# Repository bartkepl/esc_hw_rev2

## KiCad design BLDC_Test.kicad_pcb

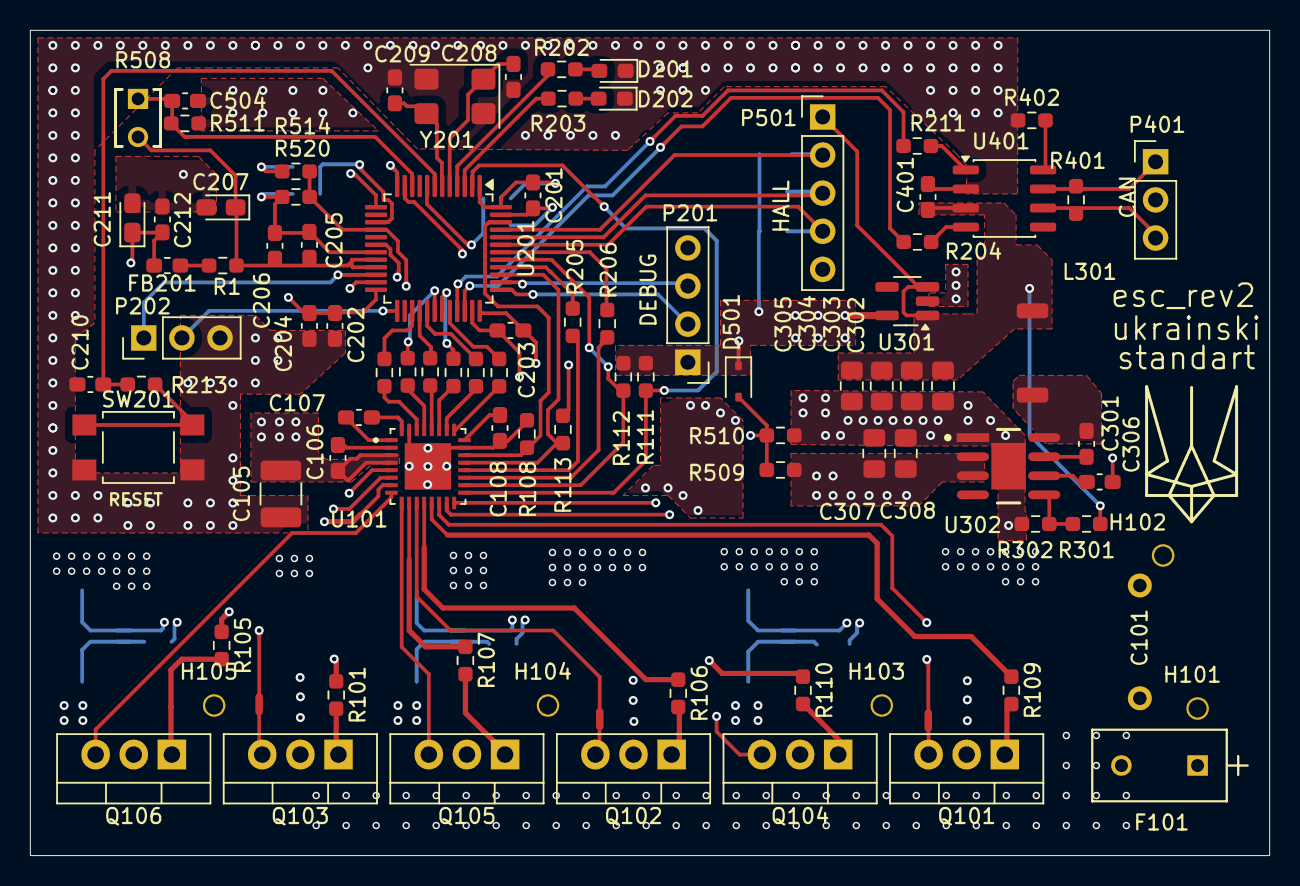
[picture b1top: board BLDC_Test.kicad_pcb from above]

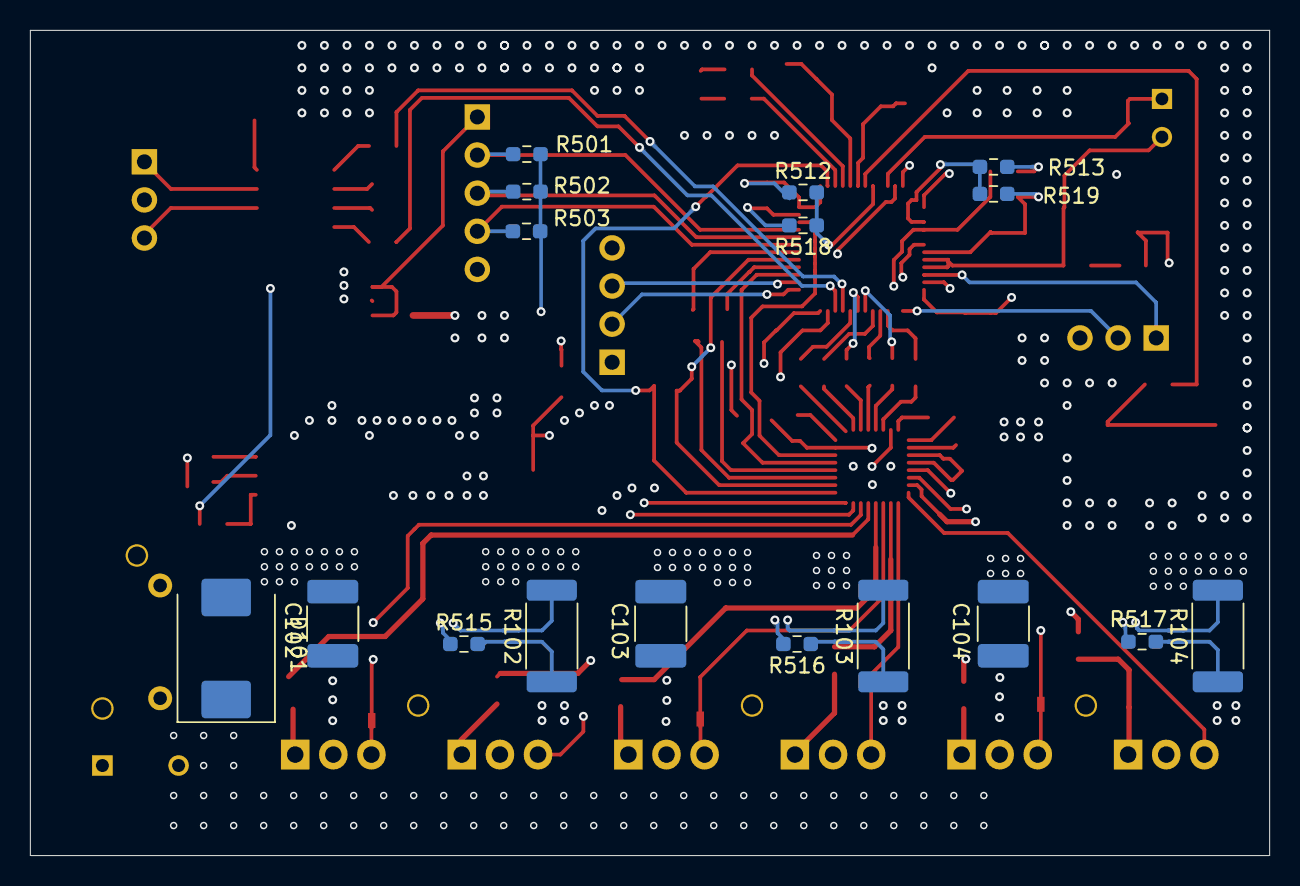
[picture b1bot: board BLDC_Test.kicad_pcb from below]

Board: 6 copper layers, 82.6 x 55.0 mm, 115 parts (23 on the bottom side), 89 nets.

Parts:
C101: 1000uF; PCAP_7_5mm
C102, C103, C104: 1812B105K101CT; C_1812_4532Metric_Pad1.57x3.40mm_HandSolder
C105: 0.1u; C_1210_3225Metric_Pad1.33x2.70mm_HandSolder
C106, C108, C306: 1u; C_0603_1608Metric_Pad1.08x0.95mm_HandSolder
C107: 47n; C_0603_1608Metric_Pad1.08x0.95mm_HandSolder
C201: 4.7uF; C_0603_1608Metric_Pad1.08x0.95mm_HandSolder
C202, C203, C204, C205, C206, C212: 100nF; C_0603_1608Metric_Pad1.08x0.95mm_HandSolder
C207, C211: 10uF; CP_EIA-2012-15_AVX-P_HandSolder
C208, C209: 33pF; C_0603_1608Metric_Pad1.08x0.95mm_HandSolder
C210, C301, C401: 100n; C_0603_1608Metric_Pad1.08x0.95mm_HandSolder
C302, C303, C304, C305: 22uF; C_0805_2012Metric_Pad1.18x1.45mm_HandSolder
C307: C3216X7R1H106K160AC; C_0805_2012Metric_Pad1.18x1.45mm_HandSolder
C308: KAF31BR71H224KT; C_0805_2012Metric_Pad1.18x1.45mm_HandSolder
C504: ?; C_0603_1608Metric_Pad1.08x0.95mm_HandSolder
D101: SMCJ36CA; D_SMC
D201, D202: Common diode; LED_0603_1608Metric_Pad1.05x0.95mm_HandSolder
D501: SS25FA; D_SOD-323
F101: SS-5F-10A-AP; FUSE_SS-5F_COB
FB201: BLM15BD601SZ1D; L_0603_1608Metric_Pad1.05x0.95mm_HandSolder
H101, H102, H103, H104, H105: phase connector; phase_cable_soldering_hole
L301: CDRH5D28RNP-8R0NC
NT101, NT102, NT103: net_tie; NetTie-2_SMD_Pad0.5mm
NT104, NT105, NT106, NT107, NT108, NT109: net_tie; NetTie-2_SMD_Pad0.3mm
P201: Header 4; PinHeader_1x04_P2.54mm_Vertical
P202, P401: Header 3; PinHeader_1x03_P2.54mm_Vertical
P501: Header 5; PinHeader_1x05_P2.54mm_Vertical
Q101, Q102, Q103, Q104, Q105, Q106: TK35A08N1; TO-220-3_Vertical
R1: 1; R_0603_1608Metric_Pad0.98x0.95mm_HandSolder
R101, R105, R106, R107, R109, R110: 10; R_0603_1608Metric_Pad0.98x0.95mm_HandSolder
R102, R103, R104: 20m; R_2512_6332Metric_Pad1.40x3.35mm_HandSolder
R108, R111, R113: 10k; R_0603_1608Metric_Pad0.98x0.95mm_HandSolder
R112: 1.8k; R_0603_1608Metric_Pad0.98x0.95mm_HandSolder
R201, R207, R208, R209, R210, R212, R213: 100; R_0603_1608Metric_Pad0.98x0.95mm_HandSolder
R202, R203: 220; R_0603_1608Metric_Pad0.98x0.95mm_HandSolder
R204, R205, R206, R211: 1k; R_0603_1608Metric_Pad0.98x0.95mm_HandSolder
R301: 100k; R_0603_1608Metric_Pad0.98x0.95mm_HandSolder
R302: 24.9k; R_0603_1608Metric_Pad0.98x0.95mm_HandSolder
R401: 120; R_0603_1608Metric_Pad0.98x0.95mm_HandSolder
R402: 1k8; R_0603_1608Metric_Pad0.98x0.95mm_HandSolder
R501, R502, R503: 4.7k; R_0603_1608Metric_Pad0.98x0.95mm_HandSolder
R508: NTCLE100E3224JB0; FP-NTCLE100E3224JB0-MFG
R509: 300k; R_0603_1608Metric_Pad0.98x0.95mm_HandSolder
R510, R511: 16k; R_0603_1608Metric_Pad0.98x0.95mm_HandSolder
R512, R513, R514: 22k; R_0603_1608Metric_Pad0.98x0.95mm_HandSolder
R515, R516, R517: 1.5k; R_0603_1608Metric_Pad0.98x0.95mm_HandSolder
R518, R519, R520: 2.2k; R_0603_1608Metric_Pad0.98x0.95mm_HandSolder
SW201: PTS647SM38SMTR2LFS; SW_SPST_TL3305A
U101: DRV8320S; QFN50P500X500X80-33N
U201: STM32G431CBTx; LQFP-48_7x7mm_P0.5mm
U301: TPS73633DBVRG4; SOT-23-5_HandSoldering
U302: LMR33630CDDAR; FP-DDA0008J-IPC_B
U401: TCAN1044VDRQ1; SO-8_3.9x4.9mm_P1.27mm
Y201: E5X080182Y03; Crystal_SMD_WE_CFPX-104-4Pin_5.0x3.2mm

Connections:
+3.3V: C108.2, U101.24 (DVDD)
+5V: C302.1, C303.1, C304.1, C305.1, C401.1, L301.2, P501.1, R301.1, U301.1 (IN), U301.3 (EN), U401.3 (VCC)
+36V: C101.1 (A), C102.1, C103.1, C104.1, C105.1, C106.1, C307.1, C308.1, D101.1 (C), F101.2, Q101.2 (D), Q102.2 (D), Q103.2 (D), R509.1, U101.3 (VM), U101.4 (VDRAIN), U302.2 (VIN), U302.3 (EN)
/can/CAN_N: P401.3, R401.2, U401.6 (CANL)
/can/CAN_P: P401.1, R401.1, U401.7 (CANH)
/inverter/CPH: C107.2, U101.1 (CPH)
/inverter/CPL: C107.1, U101.32 (CPL)
/inverter/GHA: Q101.1 (G), R109.2
/inverter/GHB: Q102.1 (G), R106.2
/inverter/GHC: Q103.1 (G), R101.2
/inverter/GLA: Q104.1 (G), R110.2
/inverter/GLB: Q105.1 (G), R107.2
/inverter/GLC: Q106.1 (G), R105.2
/inverter/OUT_A: H103.1, NT101.1, Q101.3 (S), Q104.2 (D)
/inverter/OUT_B: H104.1, NT102.1, Q102.3 (S), Q105.2 (D)
/inverter/OUT_C: H105.1, NT103.1, Q103.3 (S), Q106.2 (D)
/inverter/SHA: NT101.2, U101.14 (SHC)
/inverter/SHB: NT102.2, U101.11 (SHB)
/inverter/SHC: NT103.2, U101.6 (SHA)
/inverter/SLA: NT104.1, Q104.3 (S), R102.1, U101.16 (SLC)
/inverter/SLB: NT105.1, Q105.3 (S), R103.1, U101.9 (SLB)
/inverter/SLC: NT106.1, Q106.3 (S), R104.1, U101.8 (SLA)
/inverter/VCP: C106.2, U101.2 (VCP)
/mcu/LED_GREEN: R202.1, U201.4 (PC15)
/mcu/LED_RED: R203.1, U201.3 (PC14)
/mcu/NRST: C210.1, R213.1, U201.7 (PG10)
/mcu/SWCLK: P201.3, U201.38 (PA14)
/mcu/SWDIO: P201.2, U201.37 (PA13)
/mcu/USART_RX: P202.2, U201.25 (PB11)
/mcu/USART_TX: P202.1, U201.22 (PB10)
CS: R113.1, U101.21 (SCS), U201.39 (PA15)
ENABLE: R108.1, U101.22 (ENABLE), U201.46 (PB9)
FAULT: R111.1, U101.17 (FAULT), U201.2 (PC13)
GND: C101.2 (B), C102.2, C103.2, C104.2, C105.2, C108.1, C201.2, C202.2, C203.2, C204.2, C205.2, C206.2, C207.2, C208.2, C209.2, C210.2, C211.2, C212.2, C302.2, C303.2, C304.2, C305.2, C306.2, C307.2, C308.2, C401.2, C504.2, D101.2 (A), D201.1 (C), D202.1 (C), H102.1, NT107.1, NT108.1, NT109.1, P201.4, P202.3, P401.2, P501.5, R102.2, R103.2, R104.2, R108.2, R302.2, R402.2, R510.2, R511.2, R518.2, R519.2, R520.2, SW201.2 (D), U101.23 (AGND), U101.31 (PGND), U101.33 (PP), U201.19 (VSSA), U201.23 (VSS), U201.35 (VSS), U201.47 (VSS), U301.2 (GND), U302.1 (PGND), U302.9 (Thermal_Pad), U401.2 (GND), Y201.2 (G), Y201.4 (G)
HALL_A: P501.4, R503.2, U201.43 (PB6)
HALL_B: P501.3, R502.2, U201.44 (PB7)
HALL_C: P501.2, R501.2, U201.45 (PB8)
MEAS_A+: R512.2, R515.1, R518.1, U201.8 (PA0)
MEAS_A-: NT107.2, U201.11 (PA3)
MEAS_B+: R513.2, R516.2, R519.1, U201.15 (PA7)
MEAS_B-: NT108.2, U201.13 (PA5)
MEAS_C+: R514.2, R517.1, R520.1, U201.16 (PB0)
MEAS_C-: NT109.2, U201.18 (PB2)
unnamed: D201.2 (A), R202.2
unnamed: D202.2 (A), R203.2
unnamed: F101.1, H101.1
unnamed: FB201.2, R1.1
unnamed: R213.2, SW201.1 (C)
unnamed: R101.1, U101.5 (GHA)
unnamed: R106.1, U101.12 (GHB)
unnamed: R109.1, U101.13 (GHC)
unnamed: R105.1, U101.7 (GLA)
unnamed: R107.1, U101.10 (GLB)
unnamed: R110.1, U101.15 (GLC)
unnamed: R207.2, U201.30 (PA8)
unnamed: R208.2, U201.31 (PA9)
unnamed: R210.2, U201.32 (PA10)
unnamed: R211.2, U201.33 (PA11)
unnamed: R204.1, U201.34 (PA12)
unnamed: R205.1, U201.40 (PB3)
unnamed: R206.1, U201.42 (PB5)
unnamed: R209.1, U201.27 (PB13)
unnamed: R212.2, U201.28 (PB14)
unnamed: R201.1, U201.29 (PB15)
unnamed: C208.1, U201.5 (PF0), Y201.1
unnamed: C209.1, U201.6 (PF1), Y201.3
unnamed: C301.2, U302.7 (BOOT)
unnamed: R301.2, R302.1, U302.5 (FB)
unnamed: C301.1, L301.1, U302.8 (SW)
unnamed: C306.1, U302.6 (VCC)
unnamed: R402.1, U401.8 (STB)
RXCAN: R211.1, U401.1 (TXD)
SCLK: R205.2, U101.20 (SCLK)
SDI: R206.2, U101.19 (SDI)
SDO: R112.1, U101.18 (SDO), U201.41 (PB4)
TEMP: C504.1, R508.1, R511.1, U201.10 (PA2)
TIMHA: R207.1, U101.29 (INHC)
TIMHB: R208.1, U101.27 (INHB)
TIMHC: R210.1, U101.25 (INHA)
TIMLA: R209.2, U101.30 (INLC)
TIMLB: R212.1, U101.28 (INLB)
TIMLC: R201.2, U101.26 (INLA)
TXCAN: R204.2, U401.4 (RXD)
VBUS: D501.2 (A), R509.2, R510.1, U201.12 (PA4)
VDD: C201.1, C202.1, C203.1, C204.1, C211.1, C212.1, D501.1 (C), FB201.1, P201.1, R111.2, R112.2, R113.2, R501.1, R502.1, R503.1, R512.1, R513.1, R514.1, U201.1 (VBAT), U201.24 (VDD), U201.36 (VDD), U201.48 (VDD), U301.5 (OUT)
VDDA: C205.1, C206.1, C207.1, R1.2, R508.2, U201.20 (VREF+), U201.21 (VDDA)
VSHUNT_A+: NT104.2, R515.2
VSHUNT_B+: NT105.2, R516.1
VSHUNT_C+: NT106.2, R517.2

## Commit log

2026-03-06 added gnd polygen layer 4
2026-03-10 final changes to the pcb
2026-03-25 Added prod files and little organization
2026-03-28 PCB mounting bom

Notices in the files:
parts and their libraries:
COPYRIGHT: Copyright (C) 2025 Ultra Librarian. All rights reserved.
